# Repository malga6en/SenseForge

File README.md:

# Sensor Measurement Board

This project is an **open hardware measurement board** designed to read sensor data using an **ESP32 NodeMCU** and publish it via **MQTT**.

## 🧠 Description
The board allows you to measure environmental parameters using the following sensors:
- **BH1750** – Ambient light intensity (lux)
- **SHTC3** – Temperature and humidity
- **PIR Sensor** – Motion detection

The ESP32 NodeMCU reads all sensor values and publishes them through MQTT topics to any subscribed client or local broker.

## ⚙️ Features
- Integrated I²C bus for BH1750 and SHTC3
- Digital input for the PIR motion sensor
- ESP32 NodeMCU for data acquisition and MQTT publishing
- Open design suitable for educational or experimental use

## 🧩 Usage
You can flash your own firmware to the ESP32 to:
- Connect to your Wi-Fi network
- Publish data to a local or remote MQTT broker
- Integrate with home automation systems (e.g., Home Assistant)

## 🪪 License
This project is licensed under the **Creative Commons Attribution-NonCommercial-ShareAlike 4.0 International License (CC BY-NC-SA 4.0)**.

You are free to:
- Share — copy and redistribute the material in any medium or format  
- Adapt — remix, transform, and build upon the material  

Under the following terms:
- **Attribution** — You must give appropriate credit.  
- **NonCommercial** — You may not use the material for commercial purposes.  
- **ShareAlike** — You must distribute your contributions under the same license.  

🔗 License details: [CC BY-NC-SA 4.0](https://creativecommons.org/licenses/by-nc-sa/4.0/)  
SPDX-License-Identifier: CC-BY-NC-SA-4.0

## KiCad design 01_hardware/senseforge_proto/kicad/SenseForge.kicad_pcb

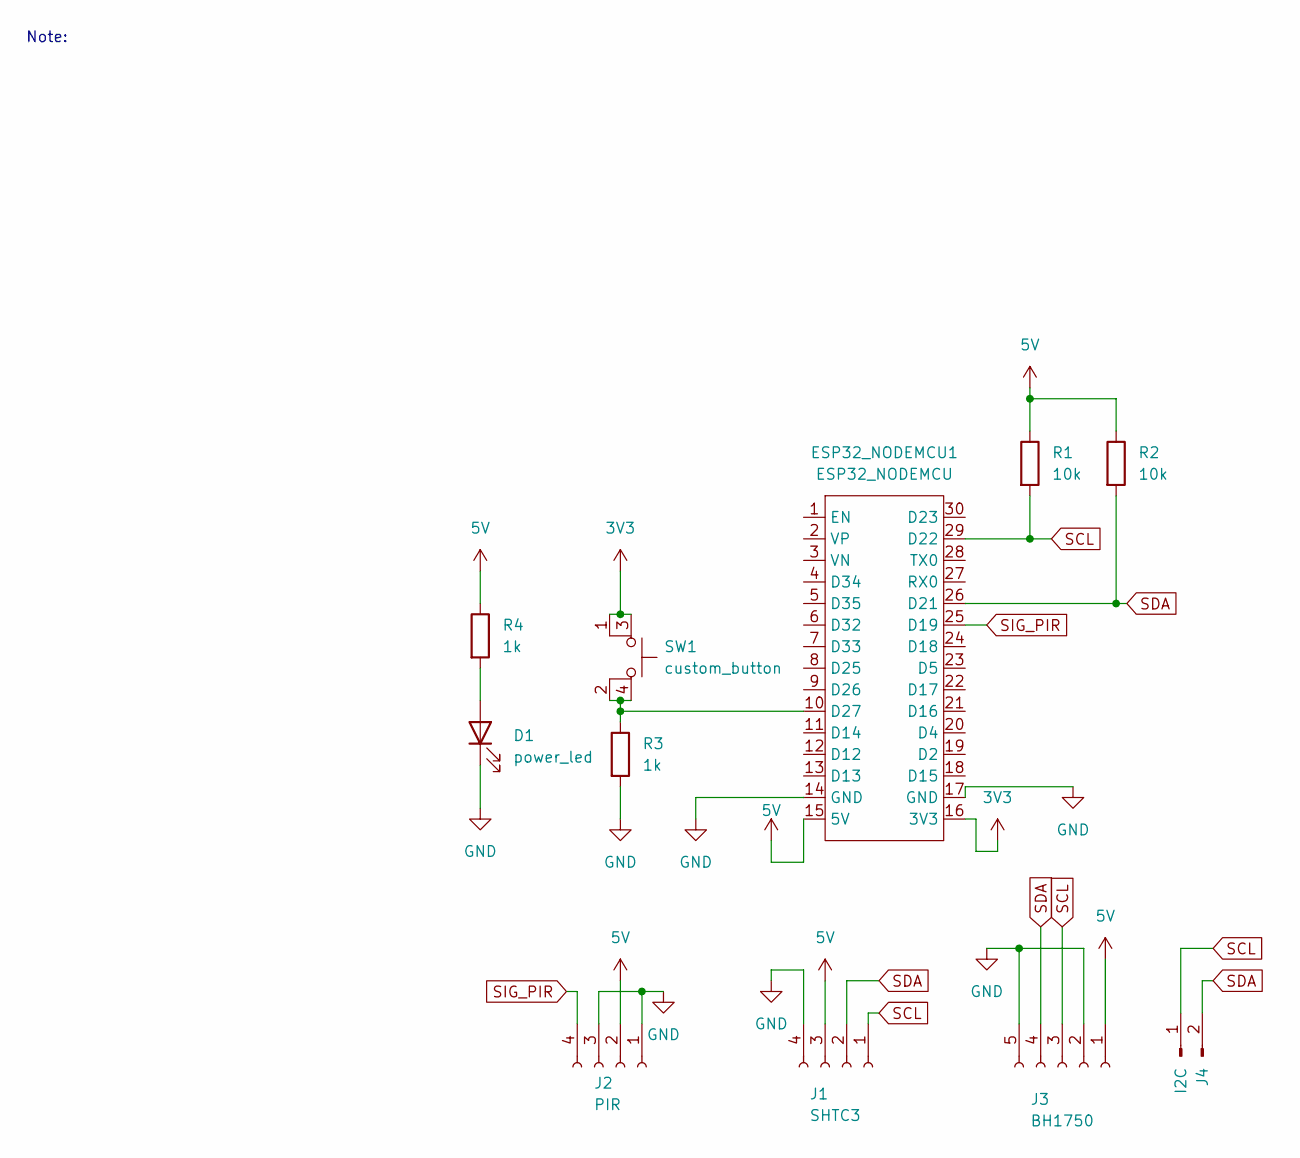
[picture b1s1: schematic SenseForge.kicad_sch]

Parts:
D1: power_led; LED_D3.0mm
ESP32_NODEMCU1: ESP32_NODEMCU
J1: SHTC3; PinSocket_1x04_P2.54mm_Vertical
J2: PIR; PinSocket_1x04_P2.54mm_Vertical
J3: BH1750; PinSocket_1x05_P2.54mm_Vertical
J4: I2C; PinHeader_1x02_P2.54mm_Vertical
R1, R2: 10k; R_0805_2012Metric; JLCPCB C17414
R3, R4: 1k; R_0805_2012Metric; JLCPCB C17513
SW1: custom_button; button_push_sms

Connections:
3V3: ESP32_NODEMCU1.16 (3V3), SW1.1 (2), SW1.3
5V: ESP32_NODEMCU1.15 (5V), J1.3, J2.2, J3.1, R1.1, R2.1, R4.1
GND: D1.1 (K), ESP32_NODEMCU1.14 (GND), ESP32_NODEMCU1.17 (GND), J1.4, J2.1, J2.3, J3.2, J3.5, R3.2
unnamed: D1.2 (A), R4.2
unnamed: ESP32_NODEMCU1.10 (D27), R3.1, SW1.2 (K), SW1.4
SCL: ESP32_NODEMCU1.29 (D22), J1.1, J3.3, J4.1, R1.2
SDA: ESP32_NODEMCU1.26 (D21), J1.2, J3.4, J4.2, R2.2
SIG_PIR: ESP32_NODEMCU1.25 (D19), J2.4

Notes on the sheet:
Note:

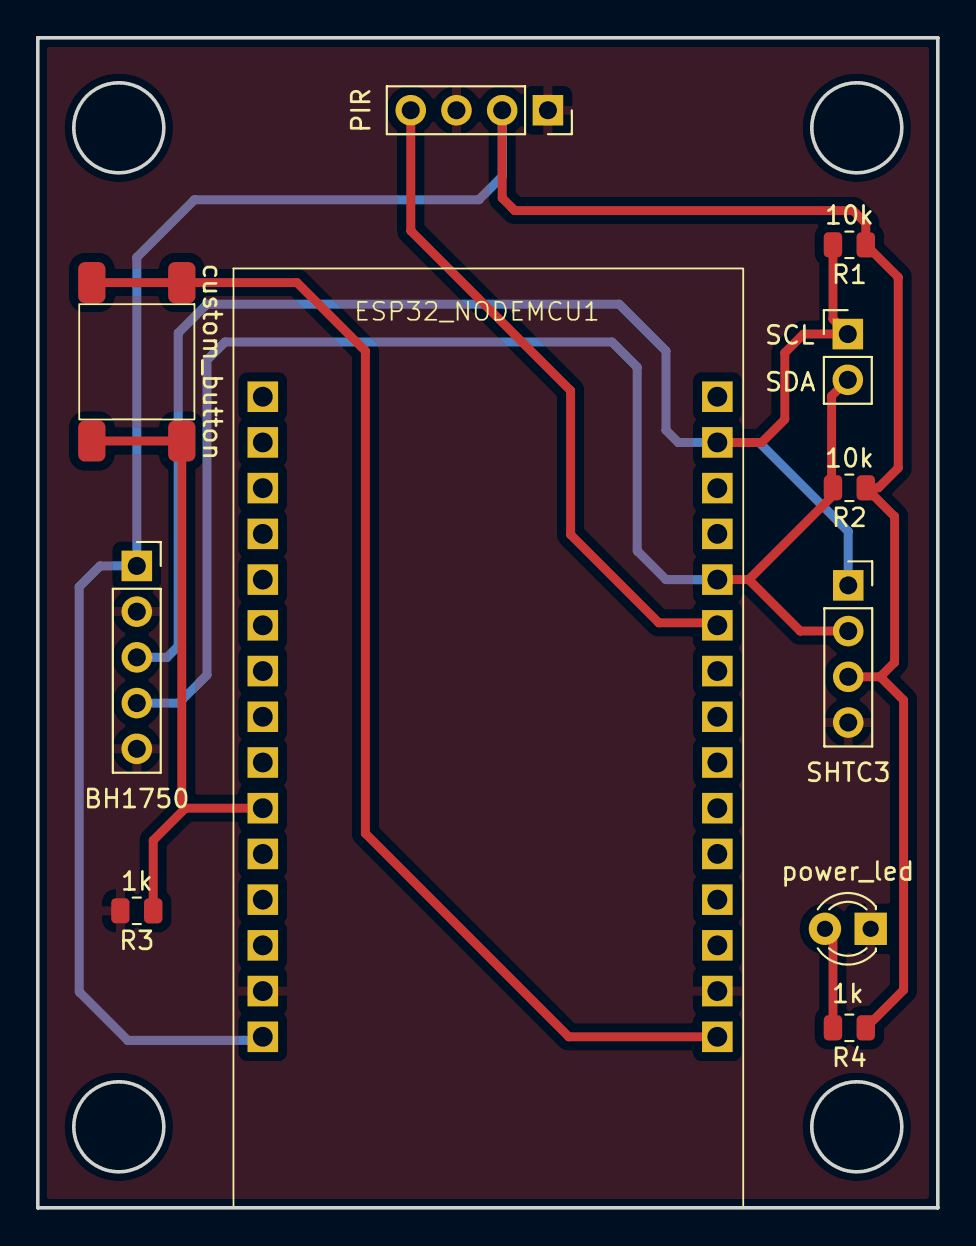
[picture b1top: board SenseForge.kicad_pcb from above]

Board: 2 copper layers, 50.0 x 65.0 mm, 11 parts (0 on the bottom side), 8 nets.

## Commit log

2025-10-31 Initial commit: Add KiCad PCB project, README, LICENSE, .gitignore
2025-10-31 Rename IoT_Station -> SenseForge; add new KiCad files
2025-11-01 JLCPCB Part no. added
2025-11-09 update: latest SenseForge PCB and schematic changes
2025-11-09 chore: update .gitignore for full KiCad + firmware project
2025-11-09 chore: normalize line endings and enable Git LFS
